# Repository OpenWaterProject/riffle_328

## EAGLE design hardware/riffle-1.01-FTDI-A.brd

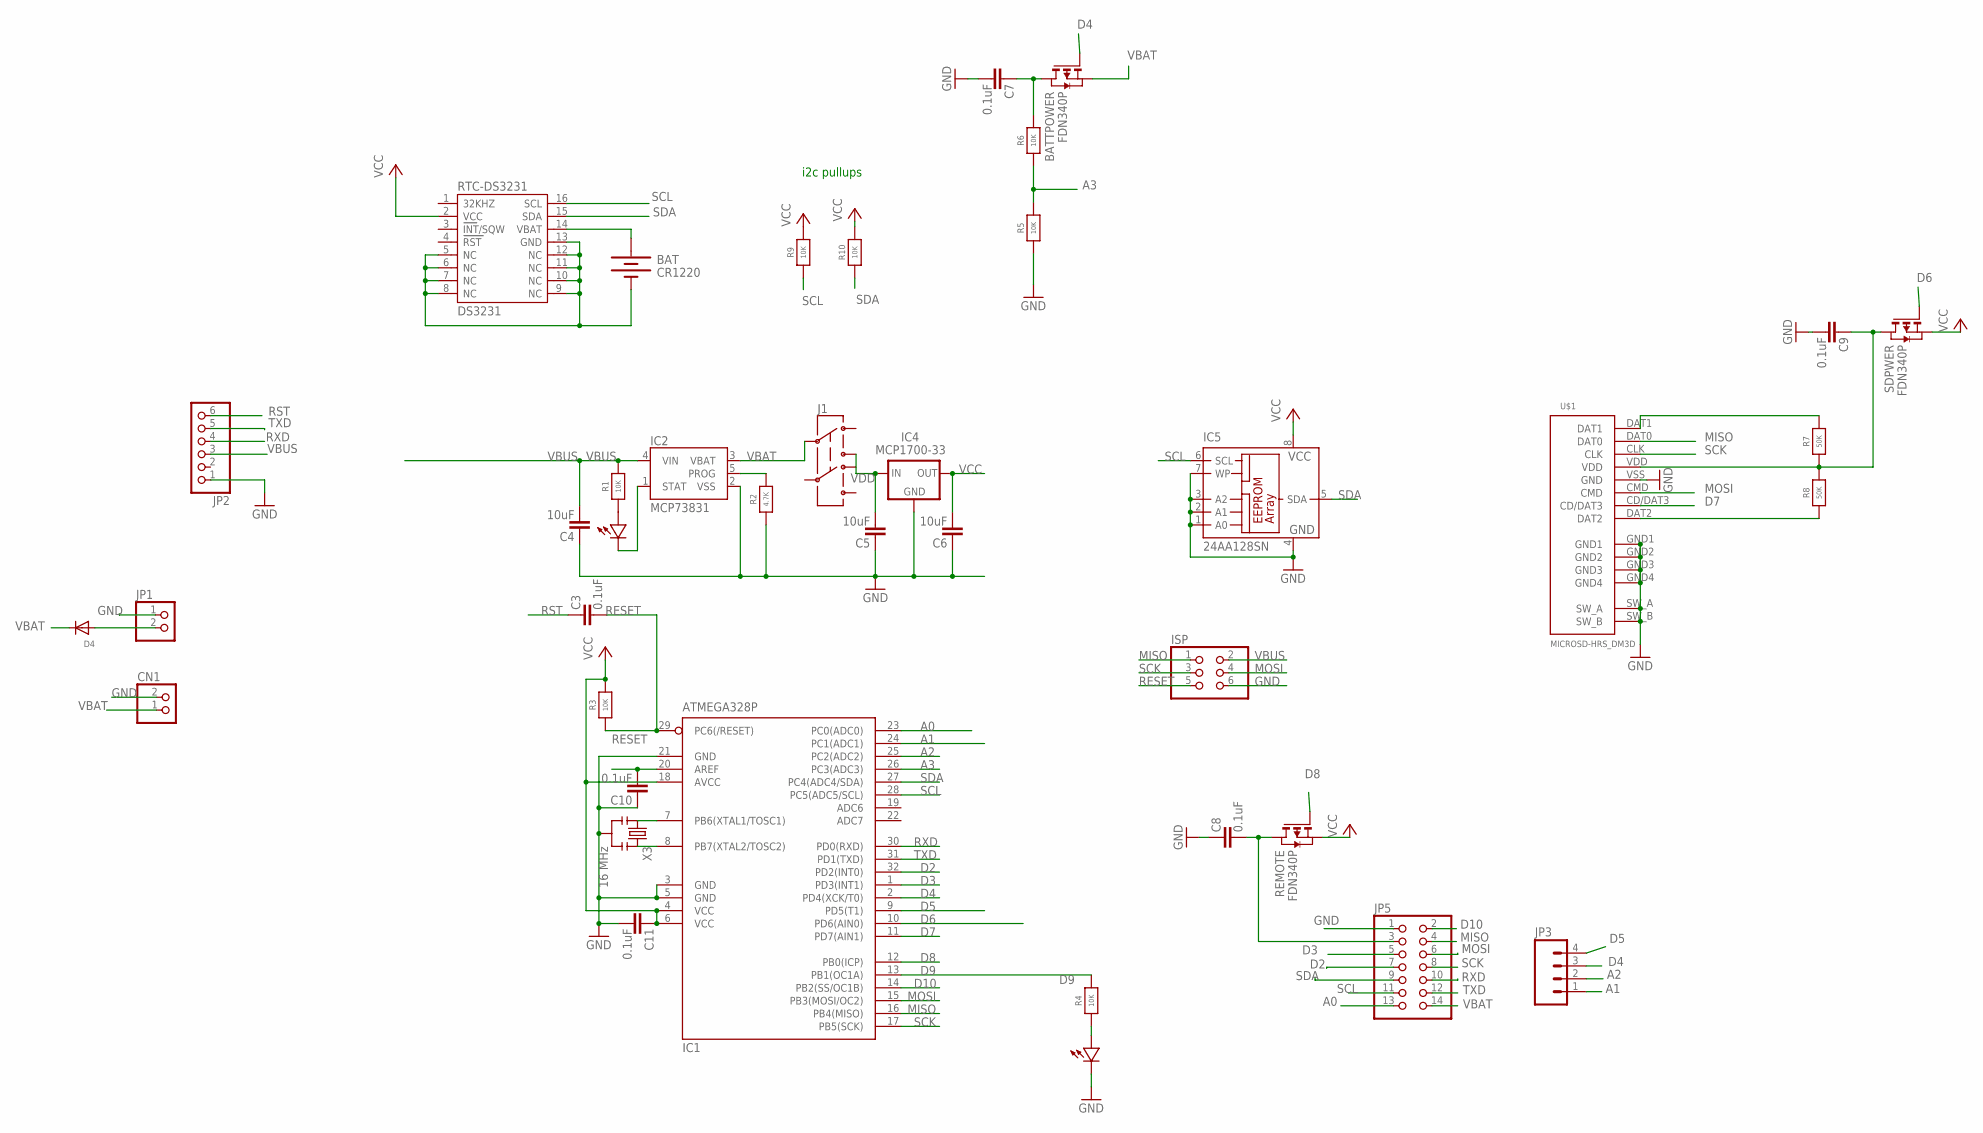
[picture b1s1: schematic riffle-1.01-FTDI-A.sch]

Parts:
BAT: CR1220; BATTCON_12MM_SMT
BATTPOWER: FDN340P; SOT-23
C3, C7, C8, C9, C10, C11: 0.1uF; 0603-CAP
C4, C5, C6: 10uF; 0603-CAP
CN1: JST_2PIN-SMT-RA; JST-PH-2-SMT-RA
D1, D2: LED0603; 0603-LED
D4: DIODESOD-323F; SOD-323F
IC1: ATMEGA328P; TQFP32-08
IC2: MCP73831; SOT23-5
IC4: MCP1700-33; SOT89
IC5: 24AA128SN; SO-08
ISP: PINHD-2X3; 2X03
J1: AYZ0202
JP1: PINHD-1X2; 1X02
JP2: PINHD-1X6; 1X06
JP3: M04SMD; 1X04-SMD
JP5: PINHD-2X7; 2X07
R1, R3, R4, R5, R6, R9, R10: 10K; 0603-NO
R2: 4.7K; 0603-NO
R7, R8: 50K; 0603-NO
REMOTE: FDN340P; SOT-23
RTC-DS3231: DS3231
SDPWER: FDN340P; SOT-23
U$1: MICROSD-HRS_DM3D; DM3D
X3: 16 MHz; RESONATOR-SMD

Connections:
A0: IC1.23 (PC0(ADC0)), JP5.13
A1: IC1.24 (PC1(ADC1)), JP3.1
A2: IC1.25 (PC2(ADC2)), JP3.2
A3: IC1.26 (PC3(ADC3)), R5.2, R6.1
AREF: C10.1, IC1.20 (AREF)
D2: IC1.32 (PD2(INT0)), JP5.7
D3: IC1.1 (PD3(INT1)), JP5.5
D4: BATTPOWER.3 (G), IC1.2 (PD4(XCK/T0)), JP3.3
D5: IC1.9 (PD5(T1)), JP3.4
D6: IC1.10 (PD6(AIN0)), SDPWER.3 (G)
D7: IC1.11 (PD7(AIN1)), U$1.CD/DAT3
D8: IC1.12 (PB0(ICP)), REMOTE.3 (G)
D9: IC1.13 (PB1(OC1A)), R4.2
D10: IC1.14 (PB2(SS/OC1B)), JP5.2
GND: BAT.P$1 (-), C4.2, C5.2, C6.2, C7.1, C8.2, C9.1, C10.2, C11.1, CN1.2 (1), D2.MINUS, IC1.3 (GND), IC1.5 (GND), IC1.21 (GND), IC2.2 (VSS), IC4.1 (GND), IC5.1 (A0), IC5.2 (A1), IC5.3 (A2), IC5.4 (GND), IC5.7 (WP), ISP.6, JP1.1, JP2.1, JP5.1, R2.1, R5.1, RTC-DS3231.5 (NC), RTC-DS3231.6 (NC), RTC-DS3231.7 (NC), RTC-DS3231.8 (NC), RTC-DS3231.9 (NC), RTC-DS3231.10 (NC), RTC-DS3231.11 (NC), RTC-DS3231.12 (NC), RTC-DS3231.13 (GND), U$1.GND1, U$1.GND2, U$1.GND3, U$1.GND4, U$1.SW_A, U$1.SW_B, U$1.VSS (GND), X3.2
MISO: IC1.16 (PB4(MISO)), ISP.1, JP5.4, U$1.DAT0
MOSI: IC1.15 (PB3(MOSI/OC2)), ISP.4, JP5.6, U$1.CMD
unnamed: D1.PLUS, R1.1
unnamed: IC1.7 (PB6(XTAL1/TOSC1)), X3.1
unnamed: IC1.8 (PB7(XTAL2/TOSC2)), X3.3
unnamed: C9.2, R7.1, R8.2, SDPWER.1 (D), U$1.VDD
unnamed: D1.MINUS, IC2.1 (STAT)
unnamed: IC2.5 (PROG), R2.2
unnamed: C8.1, JP5.3, REMOTE.1 (D)
unnamed: D4.A, JP1.2
unnamed: BATTPOWER.1 (D), C7.2, R6.2
unnamed: R7.2, U$1.DAT1
unnamed: D2.PLUS, R4.1
unnamed: R8.1, U$1.DAT2
RESET: C3.1, IC1.29 (PC6(/RESET)), ISP.5, R3.1
RST: C3.2, JP2.6
RTC_BATT: BAT.P$2 (+), RTC-DS3231.14 (VBAT)
RXD: IC1.30 (PD0(RXD)), JP2.4, JP5.10
SCK: IC1.17 (PB5(SCK)), ISP.3, JP5.8, U$1.CLK
SCL: IC1.28 (PC5(ADC5/SCL)), IC5.6 (SCL), JP5.11, R9.1, RTC-DS3231.16 (SCL)
SDA: IC1.27 (PC4(ADC4/SDA)), IC5.5 (SDA), JP5.9, R10.1, RTC-DS3231.15 (SDA)
TXD: IC1.31 (PD1(TXD)), JP2.5, JP5.12
VBAT: BATTPOWER.2 (S), CN1.1 (2), D4.C, IC2.3 (VBAT), J1.2, JP5.14
VBUS: C4.1, IC2.4 (VIN), ISP.2, JP2.3, R1.2
VCC: C6.1, C11.2, IC1.4 (VCC), IC1.6 (VCC), IC1.18 (AVCC), IC4.3 (OUT), IC5.8 (VCC), R3.2, R9.2, R10.2, REMOTE.2 (S), RTC-DS3231.2 (VCC), SDPWER.2 (S)
VDD: C5.1, IC4.2 (IN), J1.1 (3)

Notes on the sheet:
i2c pullups

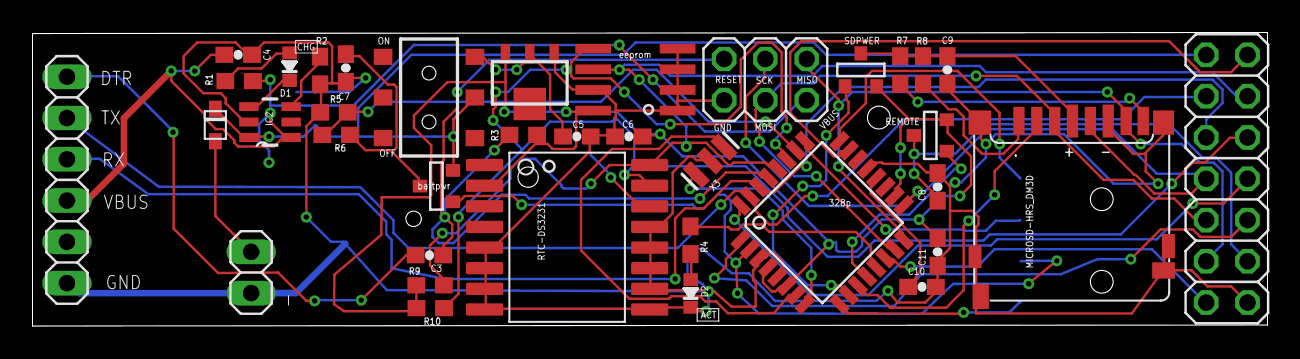
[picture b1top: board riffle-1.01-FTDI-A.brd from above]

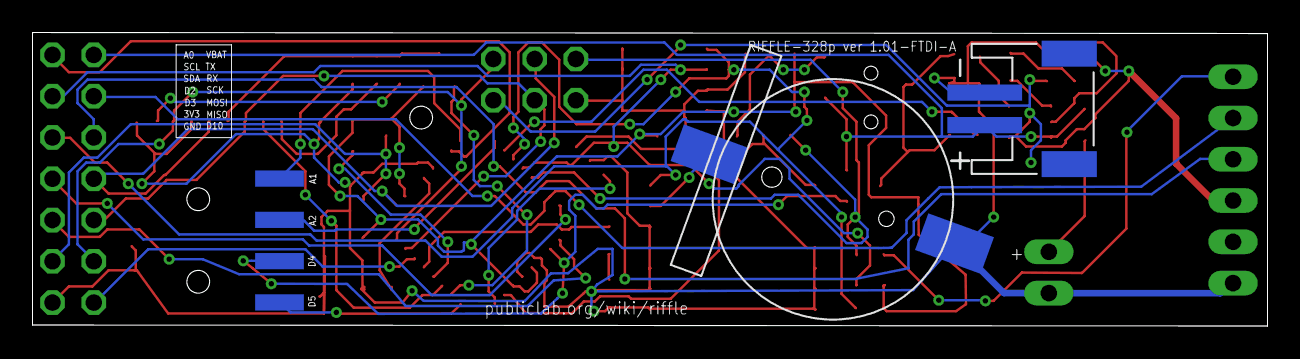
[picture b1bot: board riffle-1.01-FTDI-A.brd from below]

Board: 2 copper layers, 76.0 x 18.1 mm, 40 parts (3 on the bottom side), 41 nets.

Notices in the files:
parts and their libraries:
microbuilder: This work is placed in the public domain, and may be freely used for commercial and non-commercial work with the following conditions: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
